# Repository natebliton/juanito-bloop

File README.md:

# juanito-bloop
KiCad implementation of Juanito Moore's fun bloop circuit!

I am still a bit of a beginner in PCB layout and electronics in general, so please let me know how this could be improved! Here's a link to more of Juanito's wonderful work:
https://www.instructables.com/member/ozerik/

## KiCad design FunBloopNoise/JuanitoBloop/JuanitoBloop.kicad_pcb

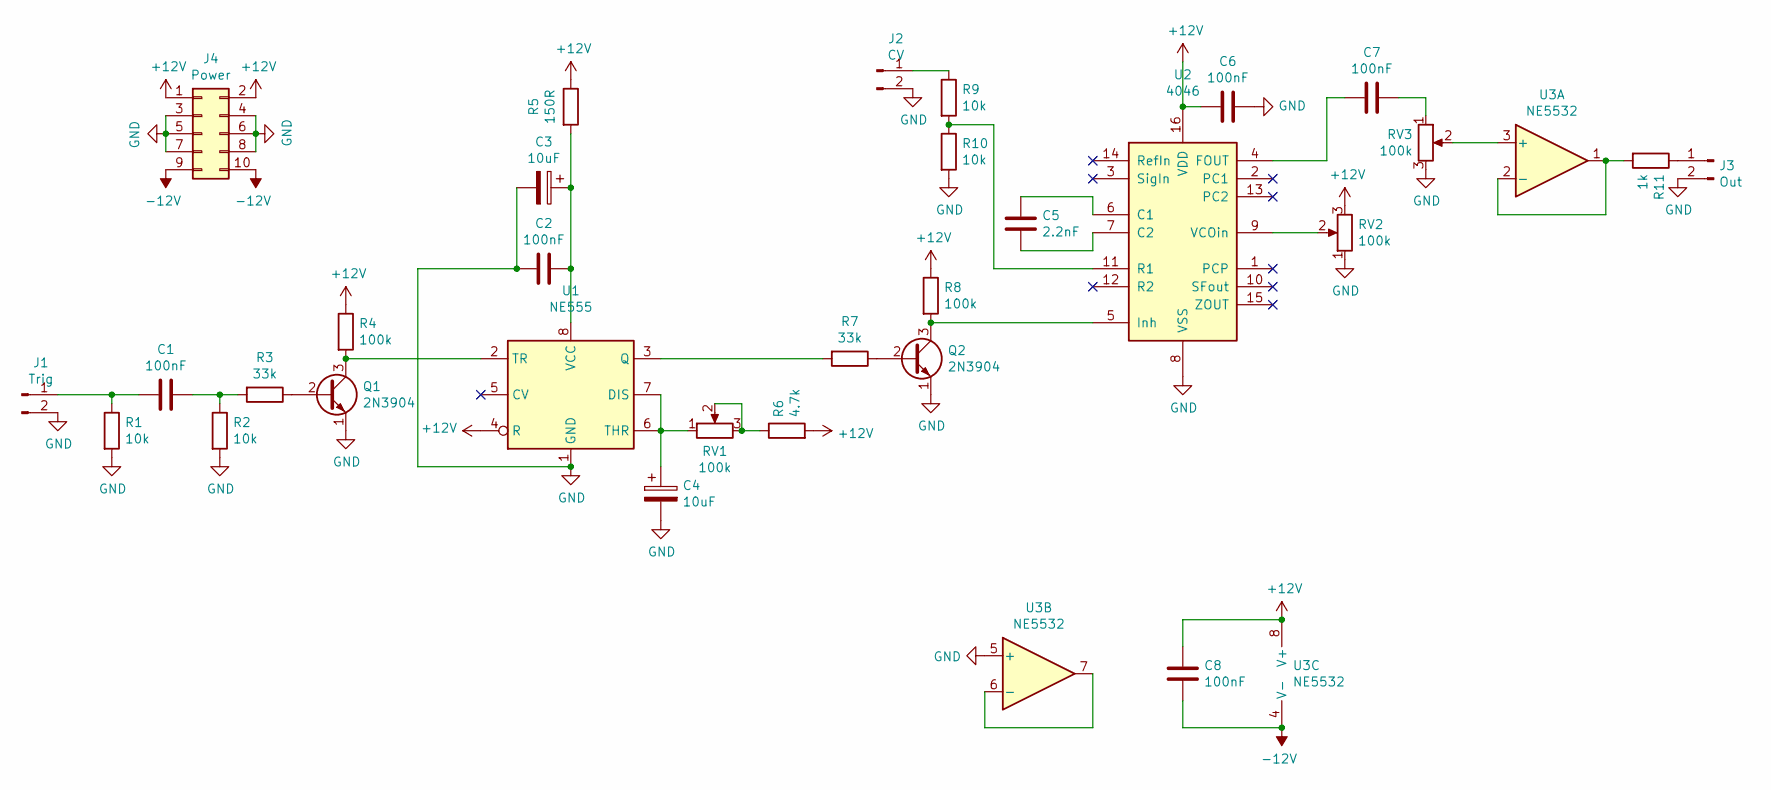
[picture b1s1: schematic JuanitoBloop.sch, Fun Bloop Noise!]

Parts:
C1, C2, C6, C7, C8: 100nF; C_Rect_L7.0mm_W2.5mm_P5.00mm
C3, C4: 10uF; CP_Radial_D5.0mm_P2.50mm
C5: 2.2nF; C_Rect_L7.0mm_W2.5mm_P5.00mm
J1: Trig; PinHeader_1x02_P2.54mm_Vertical
J2: CV; PinHeader_1x02_P2.54mm_Vertical
J3: Out; PinHeader_1x02_P2.54mm_Vertical
J4: Power; PinHeader_2x05_P2.54mm_Vertical
Q1, Q2: 2N3904; TO-92_Inline
R1, R2, R9, R10: 10k; R_Axial_DIN0207_L6.3mm_D2.5mm_P10.16mm_Horizontal
R3, R7: 33k; R_Axial_DIN0207_L6.3mm_D2.5mm_P10.16mm_Horizontal
R4, R8: 100k; R_Axial_DIN0207_L6.3mm_D2.5mm_P10.16mm_Horizontal
R5: 150R; R_Axial_DIN0207_L6.3mm_D2.5mm_P10.16mm_Horizontal
R6: 4.7k; R_Axial_DIN0207_L6.3mm_D2.5mm_P10.16mm_Horizontal
R11: 1k; R_Axial_DIN0207_L6.3mm_D2.5mm_P10.16mm_Horizontal
RV1, RV2, RV3: 100k; PinHeader_1x03_P2.54mm_Vertical
U1: NE555; DIP-8_W7.62mm_Socket_LongPads
U2: 4046; DIP-16_W7.62mm_Socket_LongPads
U3: NE5532; DIP-8_W7.62mm_Socket_LongPads

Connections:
+12V: C6.2, C8.2, J4.1, J4.2, R4.1, R5.1, R6.2, R8.1, RV2.3, U1.4 (R), U2.16 (VDD), U3.8 (V+)
-12V: C8.1, J4.9, J4.10, U3.4 (V-)
GND: C2.2, C3.2, C4.2, C6.1, J1.2, J2.2, J3.2, J4.3, J4.4, J4.5, J4.6, J4.7, J4.8, Q1.1 (E), Q2.1 (E), R1.2, R2.2, R10.2, RV2.1, RV3.3, U1.1 (GND), U2.8 (VSS), U3.5 (+)
unnamed: C1.1, R2.1, R3.2
unnamed: C1.2, J1.1, R1.1
unnamed: C2.1, C3.1, R5.2, U1.8 (VCC)
unnamed: C4.1, RV1.1, U1.6 (THR), U1.7 (DIS)
unnamed: C5.1, U2.6 (C1)
unnamed: C5.2, U2.7 (C2)
unnamed: C7.1, RV3.1
unnamed: C7.2, U2.4 (FOUT)
unnamed: J2.1, R9.1
unnamed: J3.1, R11.1
unnamed: Q1.2 (B), R3.1
unnamed: Q1.3 (C), R4.2, U1.2 (TR)
unnamed: Q2.2 (B), R7.1
unnamed: Q2.3 (C), R8.2, U2.5 (Inh)
unnamed: R6.1, RV1.2, RV1.3
unnamed: R7.2, U1.3 (Q)
unnamed: R9.2, R10.1, U2.11 (R1)
unnamed: R11.2, U3.1, U3.2 (-)
unnamed: RV2.2, U2.9 (VCOin)
unnamed: RV3.2, U3.3 (+)
unnamed: U3.6 (-), U3.7

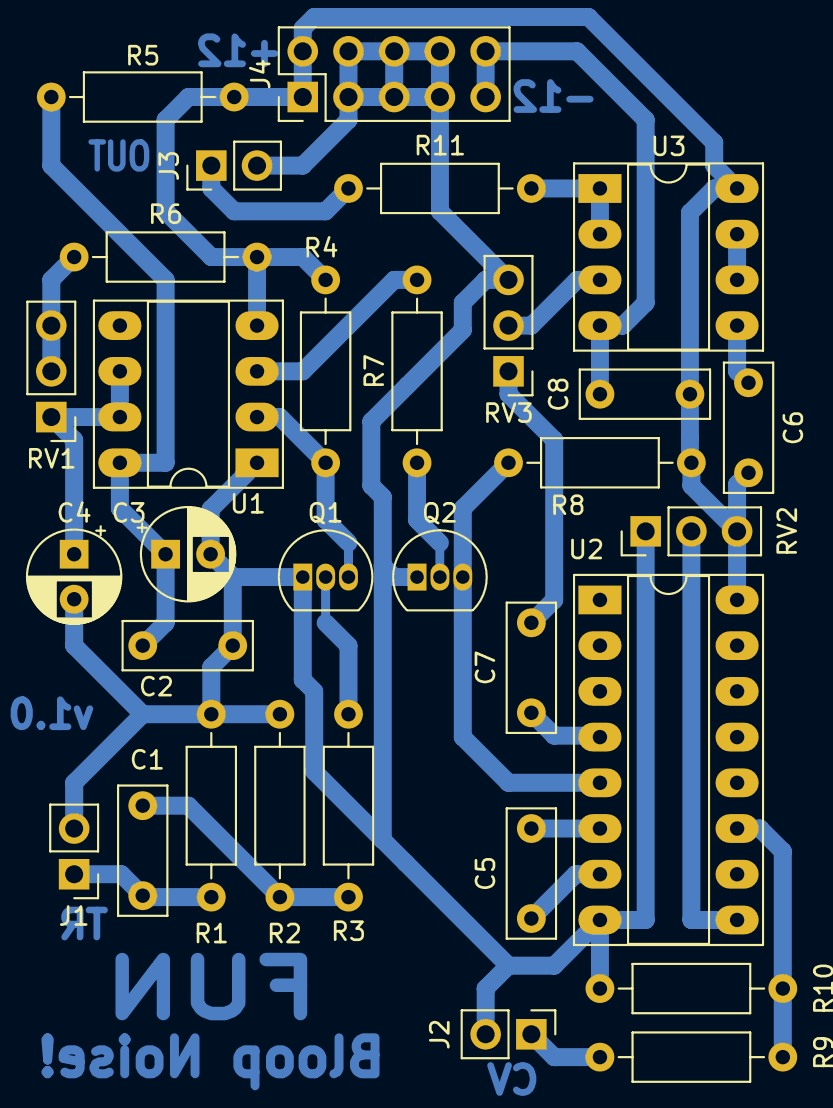
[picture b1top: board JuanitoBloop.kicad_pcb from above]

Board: 2 copper layers, 31 parts (0 on the bottom side), 24 nets.

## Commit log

2020-11-14 initial kicad project, add a couple resistors
2020-11-14 completed first pass at entering original schematic
2020-11-14 schematic v2 and pcb v1
2020-11-15 added ground plane, schematic documentation
2020-11-15 switched copper layer to back
2020-11-15 tidied up print files
2020-11-18 updated readme and notes
